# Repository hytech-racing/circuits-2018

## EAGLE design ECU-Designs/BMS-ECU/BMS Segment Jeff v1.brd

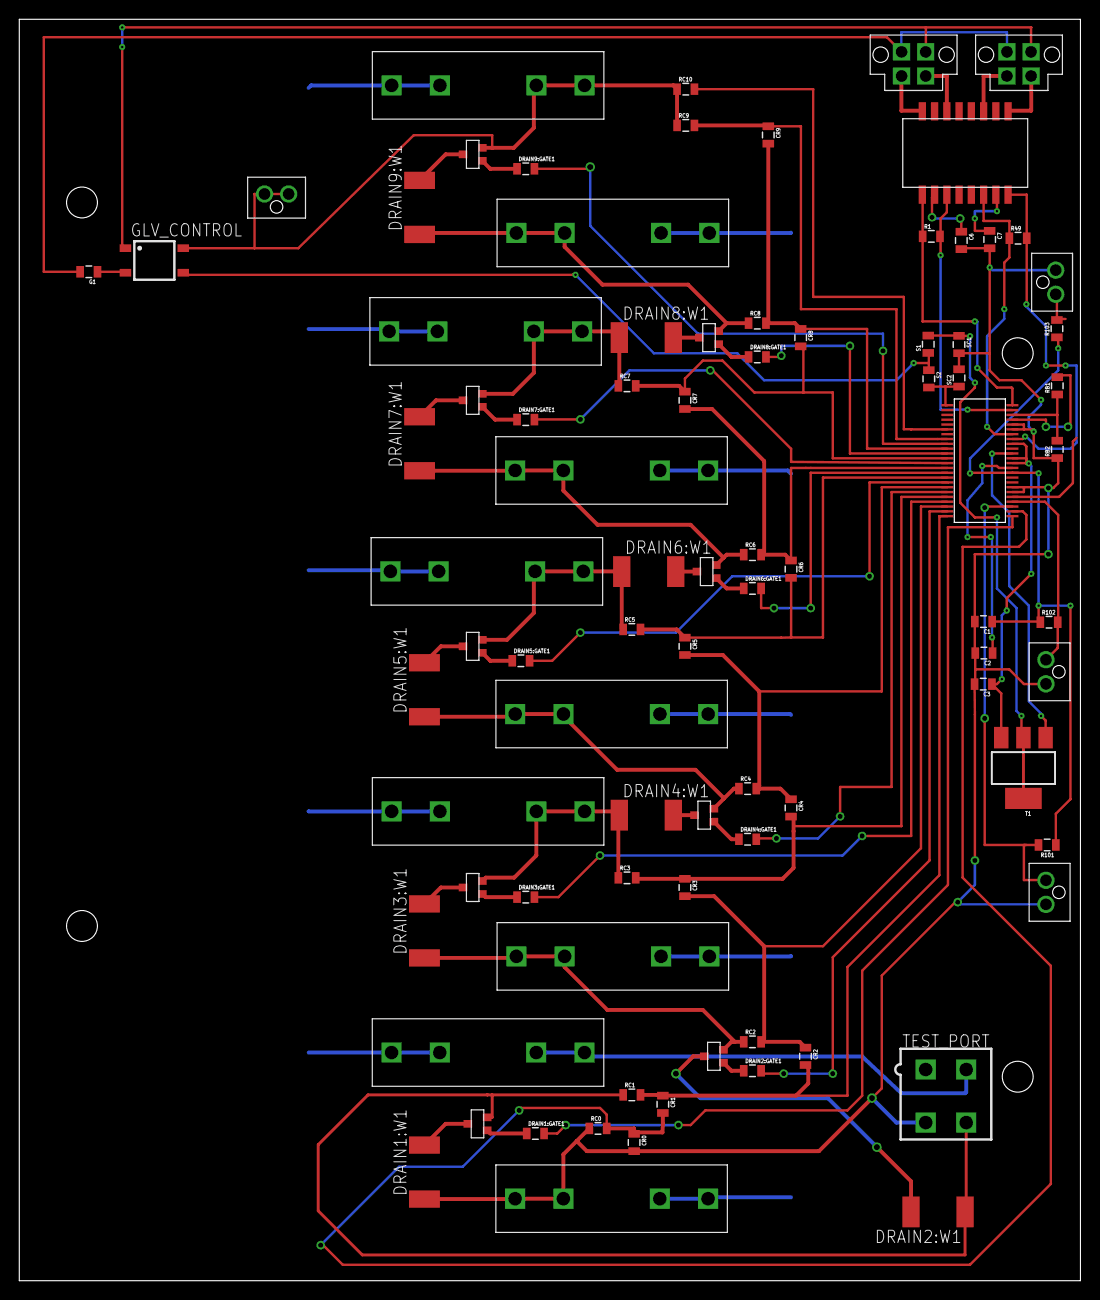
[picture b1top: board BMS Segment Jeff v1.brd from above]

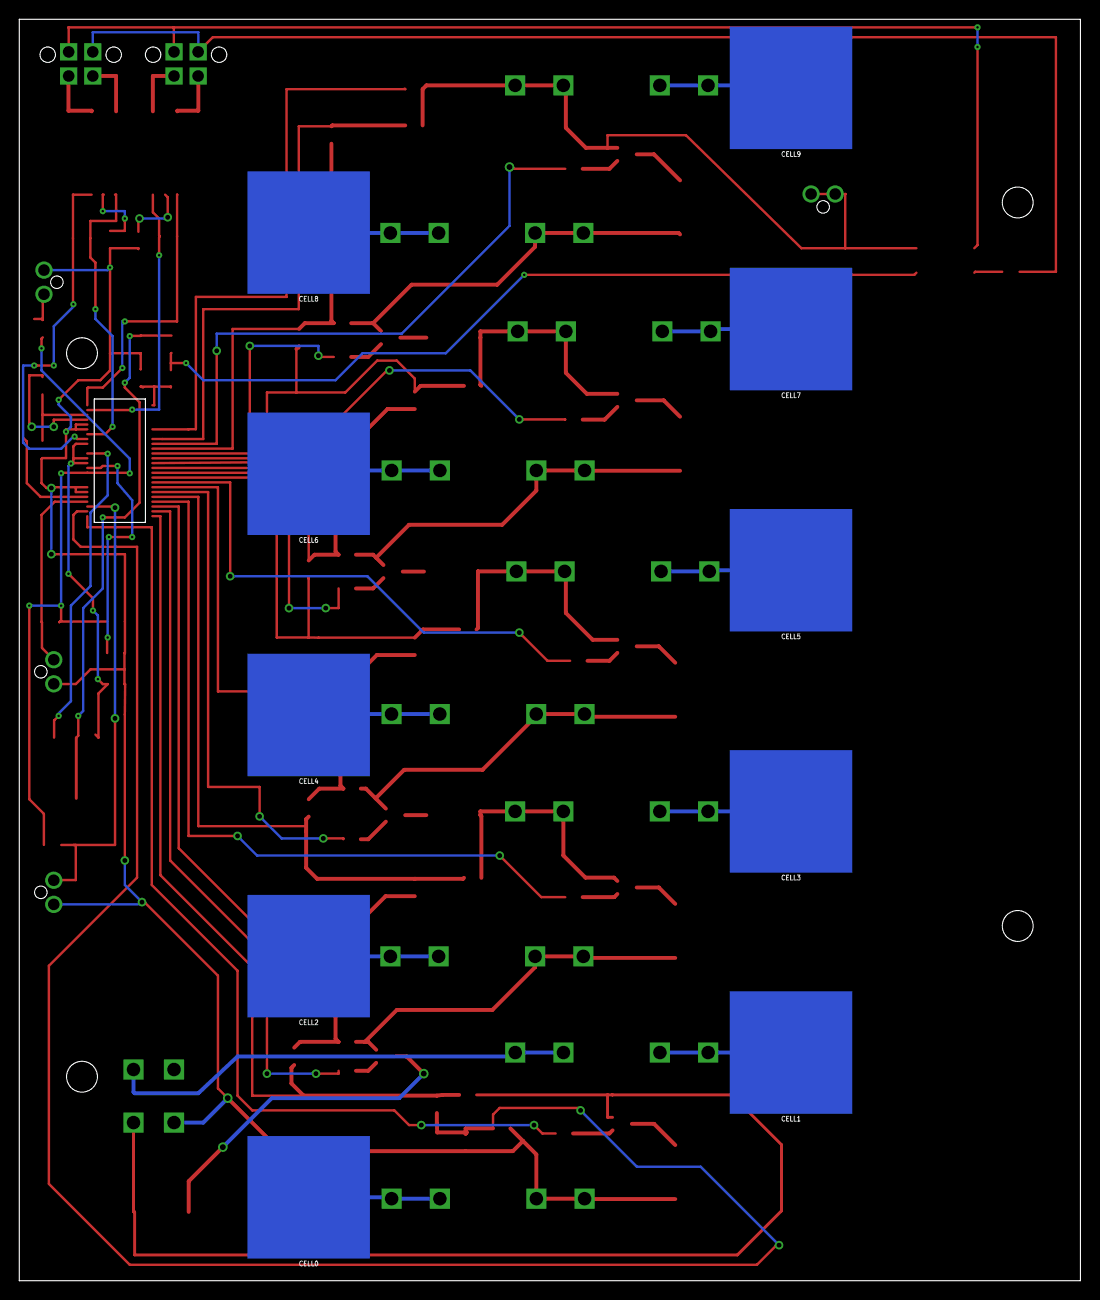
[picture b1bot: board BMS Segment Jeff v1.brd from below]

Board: 2 copper layers, 110.0 x 130.8 mm, 96 parts (10 on the bottom side), 84 nets.

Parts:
BMSIN: CONNECTOR-4NANO-FIT-VERTICAL-4; NANO-FIT_VERTICAL-4
BMSOUT: CONNECTOR-4NANO-FIT-VERTICAL-4; NANO-FIT_VERTICAL-4
C1, C2, C3: 1uF; 0805
C6, C7: 25pF; 0805
CELL0, CELL1, CELL2, CELL3, CELL4, CELL5, CELL6, CELL7, CELL8, CELL9: KEYSTONE5222
CR0, CR1, CR2, CR3, CR4, CR5, CR6, CR7, CR8, CR9: 10nF; 0805
DRAIN1:GATE1, DRAIN2:GATE1, DRAIN3:GATE1, DRAIN4:GATE1, DRAIN5:GATE1, DRAIN6:GATE1, DRAIN7:GATE1, DRAIN8:GATE1, DRAIN9:GATE1: 3.3kΩ; 0805
DRAIN1:PFET1, DRAIN2:PFET1, DRAIN3:PFET1, DRAIN4:PFET1, DRAIN5:PFET1, DRAIN6:PFET1, DRAIN7:PFET1, DRAIN8:PFET1, DRAIN9:PFET1: P-CHANNEL_MOSFET_DMP3099L-7; SOT23
DRAIN1:W1, DRAIN2:W1, DRAIN3:W1, DRAIN4:W1, DRAIN5:W1, DRAIN6:W1, DRAIN7:W1, DRAIN8:W1, DRAIN9:W1: 33Ω; R2512
F0, F1, F2, F3, F4, F5, F6, F7, F8, F9: 0751.0110
G1: 100Ω; 0805
GLV_CONTROL: CPC1002N; SOP04
R1, R49: 120Ω; 0805
R101, R102, R103: 10kΩ; 0805
RB1, RB2: 1.2k; 0805
RC0, RC1, RC2, RC3, RC4, RC5, RC6, RC7, RC8, RC9, RC10: 100Ω; 0805
S1, S2: 100Ω; 0805
SC1, SC2: 0.1uF; 0805
T1: NPN_BCP56T1; SOT223
TEST_PORT: MINIFIT_5566-4
TO_TOP: CONNECTOR-2NANO-FIT_VERTICAL-2; NANO-FIT_VERTICAL-2
TRANSFORMER-: 350uH; 749010013
U$2: LTC6804
X3: Th1; NANO-FIT_VERTICAL-2
X4: Th2; NANO-FIT_VERTICAL-2
X5: Th3; NANO-FIT_VERTICAL-2

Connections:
C0: CR0.1, CR1.2, RC0.2, U$2.26
C1: CR1.1, CR2.2, RC1.2, U$2.24
C2: CR2.1, CR3.2, RC2.2, U$2.22
C3: CR3.1, CR4.2, RC3.2, U$2.20
C4: CR4.1, CR5.2, RC4.2, U$2.18
C5: CR5.1, CR6.2, RC5.2, U$2.16
C6: CR6.1, CR7.2, RC6.2, U$2.14
C7: CR7.1, CR8.2, RC7.2, U$2.12
C8: CR8.1, CR9.2, RC8.2, U$2.10
C9: CR9.1, RC9.2, U$2.8
C10: RC10.2, U$2.6
CC0: CELL0.P$1, F0.L1, F0.L2
CC1: CELL1.P$1, F1.L1, F1.L2
CC2: CELL2.P$1, F2.L1, F2.L2
CC3: CELL3.P$1, F3.L1, F3.L2
CC4: CELL4.P$1, F4.L1, F4.L2
CC5: CELL5.P$1, F5.L1, F5.L2
CC6: CELL6.P$1, F6.L1, F6.L2
CC7: CELL7.P$1, F7.L1, F7.L2
CC8: CELL8.P$1, F8.L1, F8.L2
CC9: CELL9.P$1, F9.L1, F9.L2
DRAIN1:DRAIN: DRAIN1:PFET1.3, DRAIN1:W1.2
DRAIN1:GATE: DRAIN1:GATE1.1, DRAIN1:PFET1.1
DRAIN2:DRAIN: DRAIN2:PFET1.3, DRAIN2:W1.2
DRAIN2:GATE: DRAIN2:GATE1.1, DRAIN2:PFET1.1
DRAIN3:DRAIN: DRAIN3:PFET1.3, DRAIN3:W1.2
DRAIN3:GATE: DRAIN3:GATE1.1, DRAIN3:PFET1.1
DRAIN4:DRAIN: DRAIN4:PFET1.3, DRAIN4:W1.2
DRAIN4:GATE: DRAIN4:GATE1.1, DRAIN4:PFET1.1
DRAIN5:DRAIN: DRAIN5:PFET1.3, DRAIN5:W1.2
DRAIN5:GATE: DRAIN5:GATE1.1, DRAIN5:PFET1.1
DRAIN6:DRAIN: DRAIN6:PFET1.3, DRAIN6:W1.2
DRAIN6:GATE: DRAIN6:GATE1.1, DRAIN6:PFET1.1
DRAIN7:DRAIN: DRAIN7:PFET1.3, DRAIN7:W1.2
DRAIN7:GATE: DRAIN7:GATE1.1, DRAIN7:PFET1.1
DRAIN8:DRAIN: DRAIN8:PFET1.3, DRAIN8:W1.2
DRAIN8:GATE: DRAIN8:GATE1.1, DRAIN8:PFET1.1
DRAIN9:DRAIN: DRAIN9:PFET1.3, DRAIN9:W1.2
DRAIN9:GATE: DRAIN9:GATE1.1, DRAIN9:PFET1.1
DRIVE: T1.1, U$2.38
GND: BMSIN.P$2, BMSOUT.P$2, G1.2
ISOSPI-M_IN: BMSIN.P$3, TRANSFORMER-.8
ISOSPI-M_OUT: BMSOUT.P$3, TRANSFORMER-.3
ISOSPI-P_IN: BMSIN.P$4, TRANSFORMER-.6
ISOSPI-P_OUT: BMSOUT.P$4, TRANSFORMER-.1
unnamed: C7.1, TRANSFORMER-.10
unnamed: C6.1, TRANSFORMER-.15
unnamed: RB1.2, U$2.45
unnamed: R1.1, TRANSFORMER-.16, U$2.48
unnamed: RB1.1, RB2.2, U$2.46
unnamed: R49.1, TRANSFORMER-.11, U$2.42
unnamed: R49.2, TRANSFORMER-.9, U$2.41
unnamed: R1.2, TRANSFORMER-.14, U$2.47
S1: DRAIN1:GATE1.2, U$2.25
S2: DRAIN2:GATE1.2, U$2.23
S3: DRAIN3:GATE1.2, U$2.21
S4: DRAIN4:GATE1.2, U$2.19
S5: DRAIN5:GATE1.2, U$2.17
S6: DRAIN6:GATE1.2, U$2.15
S7: DRAIN7:GATE1.2, U$2.13
S8: DRAIN8:GATE1.2, U$2.11
S9: DRAIN9:GATE1.2, U$2.9
SENSE1: F1.R1, F1.R2, TEST_PORT.2
SENSE1_J: DRAIN1:PFET1.2, DRAIN2:W1.1, RC1.1, TEST_PORT.4
SENSE2: DRAIN2:PFET1.2, DRAIN3:W1.1, F2.R1, F2.R2, RC2.1
SENSE3: DRAIN3:PFET1.2, DRAIN4:W1.1, F3.R1, F3.R2, RC3.1
SENSE4: DRAIN4:PFET1.2, DRAIN5:W1.1, F4.R1, F4.R2, RC4.1
SENSE5: DRAIN5:PFET1.2, DRAIN6:W1.1, F5.R1, F5.R2, RC5.1
SENSE6: DRAIN6:PFET1.2, DRAIN7:W1.1, F6.R1, F6.R2, RC6.1
SENSE7: DRAIN7:PFET1.2, DRAIN8:W1.1, F7.R1, F7.R2, RC7.1
SENSE8: DRAIN8:PFET1.2, DRAIN9:W1.1, F8.R1, F8.R2, RC8.1
SENSE9: DRAIN9:PFET1.2, F9.R1, F9.R2, GLV_CONTROL.4, RC9.1, RC10.1, TO_TOP.P$1, TO_TOP.P$2
SHUTDOWN_CIRCUIT: BMSIN.P$1, BMSOUT.P$1, GLV_CONTROL.1
SSR-: G1.1, GLV_CONTROL.2
SUPPLY: S1.2, SC1.1, T1.2, T1.4
SUPPLY_INTER: GLV_CONTROL.3, S1.1, S2.1
THERMISTOR1: R101.2, U$2.27, X5.P$2
THERMISTOR2: R102.2, U$2.28, X4.P$2
THERMISTOR3: R103.2, U$2.29, X3.P$2
V+: S2.2, SC2.1, U$2.1
V-: C1.2, C2.2, C3.2, C6.2, C7.2, CR0.2, DRAIN1:W1.1, F0.R1, F0.R2, RB2.1, RC0.1, SC1.2, SC2.2, TEST_PORT.3, U$2.30, U$2.31, U$2.43, U$2.44, X3.P$1, X4.P$1, X5.P$1
VREF1: C2.1, U$2.35
VREF2: C1.1, R101.1, R102.1, R103.1, U$2.34
VREG: C3.1, T1.3, U$2.36, U$2.37, U$2.40

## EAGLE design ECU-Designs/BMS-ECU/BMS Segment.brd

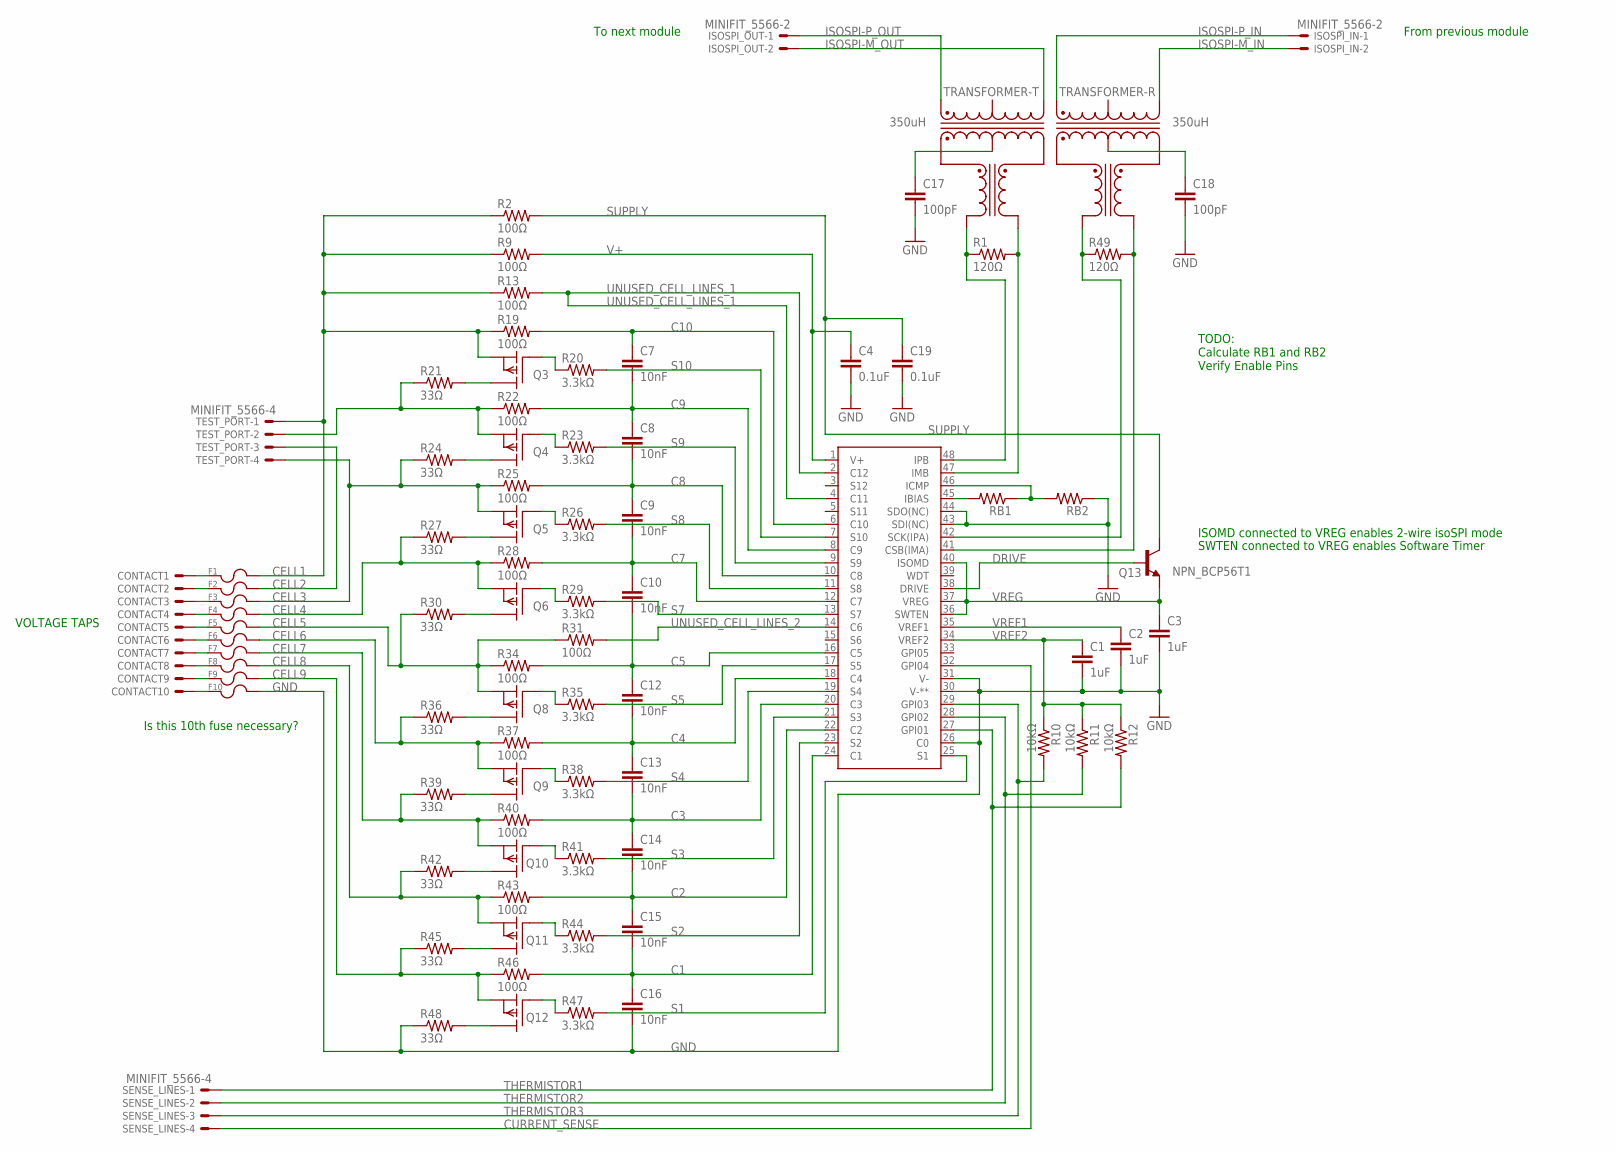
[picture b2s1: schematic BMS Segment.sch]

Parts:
C1, C2, C3: 1uF; 0805
C4, C19: 0.1uF; 0805
C7, C8, C9, C10, C12, C13, C14, C15, C16: 10nF; 0805
C17, C18: 100pF; 0805
CONTACT1, CONTACT2, CONTACT3, CONTACT4, CONTACT5, CONTACT6, CONTACT7, CONTACT8, CONTACT9, CONTACT10: SPRING_CONTACT; S1791-42R
F1, F2, F3, F4, F5, F6, F7, F8, F9, F10: 0751.0110_FUSE_CLIP; 0751.0110
ISOSPI_IN: MINIFIT_5566-2
ISOSPI_OUT: MINIFIT_5566-2
Q3, Q4, Q5, Q6, Q8, Q9, Q10, Q11, Q12: P-CHANNEL_MOSFET_DMP3099L-7; SOT23
Q13: NPN_BCP56T1; SOT223
R1, R49: 120Ω; 0805
R2, R9, R13, R19, R22, R25, R28, R31, R34, R37, R40, R43, R46: 100Ω; 0805
R10, R11, R12: 10kΩ; 0805
R20, R23, R26, R29, R35, R38, R41, R44, R47: 3.3kΩ; 0805
R21, R24, R27, R30, R36, R39, R42, R45, R48: 33Ω; R2512
RB1, RB2: RESISTOR0805-RES; 0805
SENSE_LINES: MINIFIT_5566-4
TEST_PORT: MINIFIT_5566-4
TRANSFORMER-: 350uH; 749010013
U$2: LTC6804-1; LTC6804

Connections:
C1: C15.2, C16.1, R46.2, U$2.24 (C1)
C2: C14.2, C15.1, R43.2, U$2.22 (C2)
C3: C13.2, C14.1, R40.2, U$2.20 (C3)
C4: C12.2, C13.1, R37.2, U$2.18 (C4)
C5: C10.2, C12.1, R34.2, U$2.16 (C5)
C7: C9.2, C10.1, R28.2, U$2.12 (C7)
C8: C8.2, C9.1, R25.2, U$2.10 (C8)
C9: C7.2, C8.1, R22.2, U$2.8 (C9)
C10: C7.1, R19.2, U$2.6 (C10)
CELL1: F1.R1 (2), F1.R2 (2), Q3.2 (S), R2.1, R9.1, R13.1, R19.1, TEST_PORT.1
CELL2: F2.R1 (2), F2.R2 (2), Q4.2 (S), R21.1, R22.1, TEST_PORT.2, TEST_PORT.3
CELL3: F3.R1 (2), F3.R2 (2), Q5.2 (S), R24.1, R25.1, TEST_PORT.4
CELL4: F4.R1 (2), F4.R2 (2), Q6.2 (S), R27.1, R28.1
CELL5: F5.R1 (2), F5.R2 (2), Q8.2 (S), R30.1, R31.1, R34.1
CELL6: F6.R1 (2), F6.R2 (2), Q9.2 (S), R36.1, R37.1
CELL7: F7.R1 (2), F7.R2 (2), Q10.2 (S), R39.1, R40.1
CELL8: F8.R1 (2), F8.R2 (2), Q11.2 (S), R42.1, R43.1
CELL9: F9.R1 (2), F9.R2 (2), Q12.2 (S), R45.1, R46.1
CURRENT_SENSE: SENSE_LINES.4, U$2.32 (GPI04)
DRIVE: Q13.1 (BASE), U$2.38 (DRIVE)
GND: C1.2, C2.2, C3.2, C4.2, C16.2, C17.2, C18.2, C19.2, F10.R1 (2), F10.R2 (2), R48.1, RB2.1, U$2.26 (C0), U$2.30 (V-**), U$2.31 (V-), U$2.43 (SDI(NC)), U$2.44 (SDO(NC))
ISOSPI-M_IN: ISOSPI_IN.2, TRANSFORMER-.8 (D-)
ISOSPI-M_OUT: ISOSPI_OUT.2, TRANSFORMER-.3 (D-)
ISOSPI-P_IN: ISOSPI_IN.1, TRANSFORMER-.6 (D+)
ISOSPI-P_OUT: ISOSPI_OUT.1, TRANSFORMER-.1 (D+)
unnamed: C18.1, TRANSFORMER-.10 (CX)
unnamed: C17.1, TRANSFORMER-.15 (CX)
unnamed: RB1.2, U$2.45 (IBIAS)
unnamed: R1.1, TRANSFORMER-.16 (X+), U$2.48 (IPB)
unnamed: RB1.1, RB2.2, U$2.46 (ICMP)
unnamed: R49.1, TRANSFORMER-.11 (X+), U$2.42 (SCK(IPA))
unnamed: R49.2, TRANSFORMER-.9 (X-), U$2.41 (CSB(IMA))
unnamed: CONTACT1.P$1, F1.L1 (1), F1.L2 (1)
unnamed: Q3.1 (G), R20.1
unnamed: CONTACT2.P$1, F2.L1 (1), F2.L2 (1)
unnamed: CONTACT3.P$1, F3.L1 (1), F3.L2 (1)
unnamed: Q3.3 (D), R21.2
unnamed: CONTACT4.P$1, F4.L1 (1), F4.L2 (1)
unnamed: Q8.1 (G), R35.1
unnamed: Q9.1 (G), R38.1
unnamed: CONTACT5.P$1, F5.L1 (1), F5.L2 (1)
unnamed: CONTACT6.P$1, F6.L1 (1), F6.L2 (1)
unnamed: Q4.3 (D), R24.2
unnamed: CONTACT7.P$1, F7.L1 (1), F7.L2 (1)
unnamed: Q10.1 (G), R41.1
unnamed: Q11.1 (G), R44.1
unnamed: Q12.1 (G), R47.1
unnamed: Q5.3 (D), R27.2
unnamed: CONTACT8.P$1, F8.L1 (1), F8.L2 (1)
unnamed: CONTACT9.P$1, F9.L1 (1), F9.L2 (1)
unnamed: CONTACT10.P$1, F10.L1 (1), F10.L2 (1)
unnamed: Q6.3 (D), R30.2
unnamed: R1.2, TRANSFORMER-.14 (X-), U$2.47 (IMB)
unnamed: Q8.3 (D), R36.2
unnamed: Q9.3 (D), R39.2
unnamed: Q10.3 (D), R42.2
unnamed: Q11.3 (D), R45.2
unnamed: Q12.3 (D), R48.2
unnamed: Q4.1 (G), R23.1
unnamed: Q5.1 (G), R26.1
unnamed: Q6.1 (G), R29.1
S1: R47.2, U$2.25 (S1)
S2: R44.2, U$2.23 (S2)
S3: R41.2, U$2.21 (S3)
S4: R38.2, U$2.19 (S4)
S5: R35.2, U$2.17 (S5)
S7: R29.2, U$2.13 (S7)
S8: R26.2, U$2.11 (S8)
S9: R23.2, U$2.9 (S9)
S10: R20.2, U$2.7 (S10)
SUPPLY: C19.1, Q13.2 (COLLECTOR), Q13.4 (COLLECTOR), R2.2
THERMISTOR1: R12.2, SENSE_LINES.1, U$2.27 (GPI01)
THERMISTOR2: R11.2, SENSE_LINES.2, U$2.28 (GPI02)
THERMISTOR3: R10.2, SENSE_LINES.3, U$2.29 (GPI03)
UNUSED_CELL_LINES_1: R13.2, U$2.2 (C12), U$2.4 (C11)
UNUSED_CELL_LINES_2: R31.2, U$2.14 (C6)
V+: C4.1, R9.2, U$2.1 (V+)
VREF1: C2.1, U$2.35 (VREF1)
VREF2: C1.1, R10.1, R11.1, R12.1, U$2.34 (VREF2)
VREG: C3.1, Q13.3 (EMITTER), U$2.36 (SWTEN), U$2.37 (VREG), U$2.40 (ISOMD)

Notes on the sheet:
SWTEN connected to VREG enables Software Timer
ISOMD connected to VREG enables 2-wire isoSPI mode
VOLTAGE TAPS
To next module
From previous module
TODO: Calculate RB1 and RB2 Verify Enable Pins
Is this 10th fuse necessary?

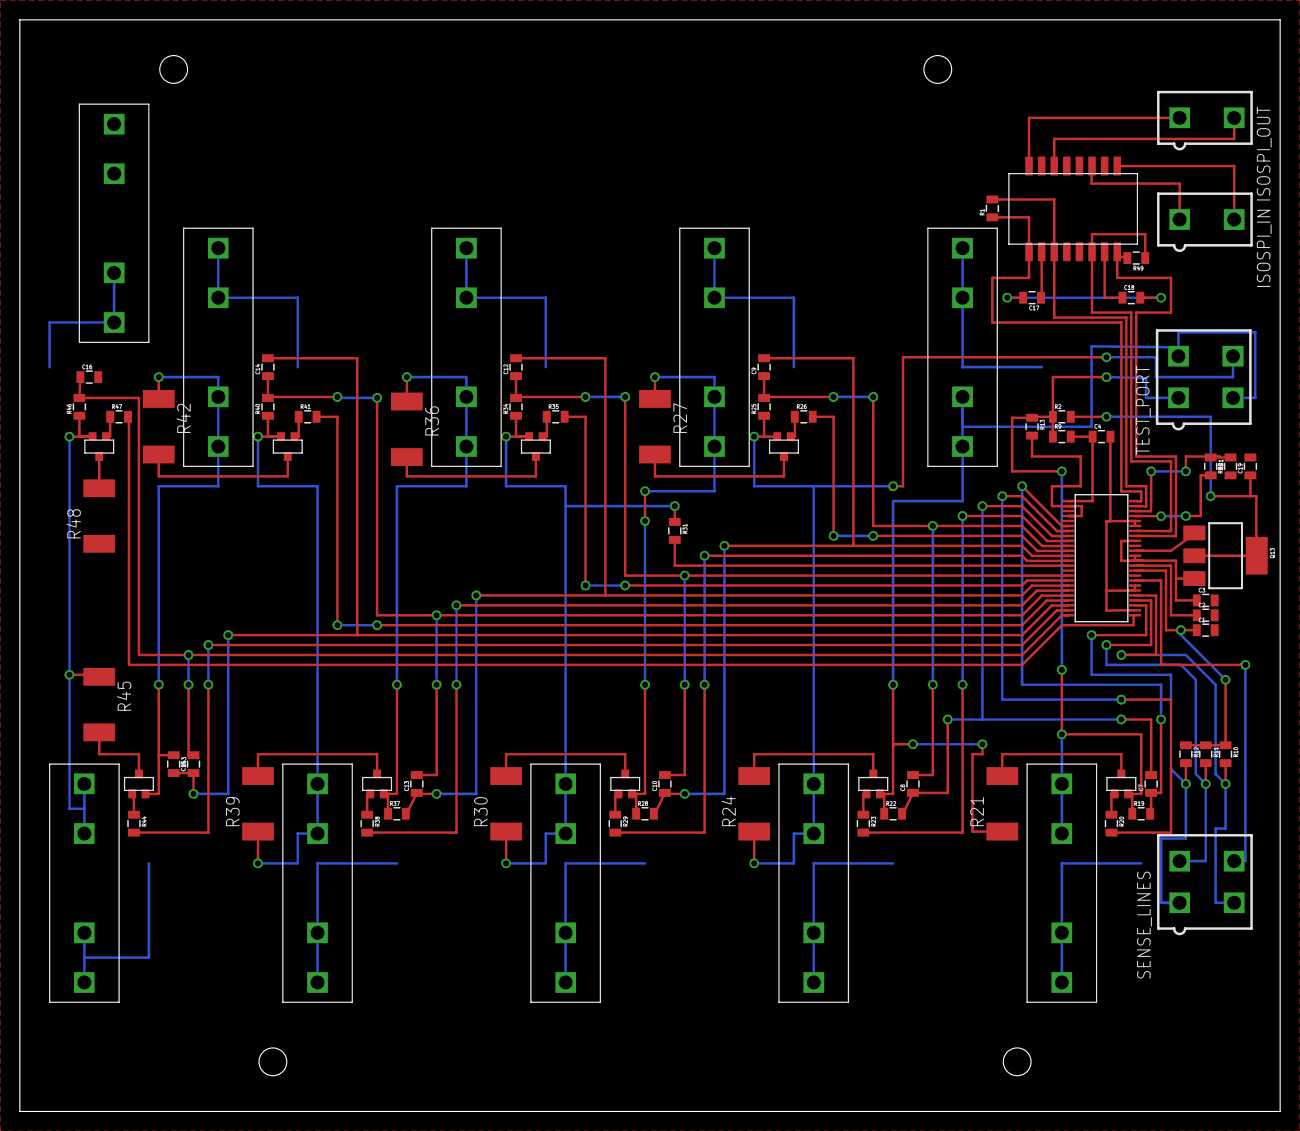
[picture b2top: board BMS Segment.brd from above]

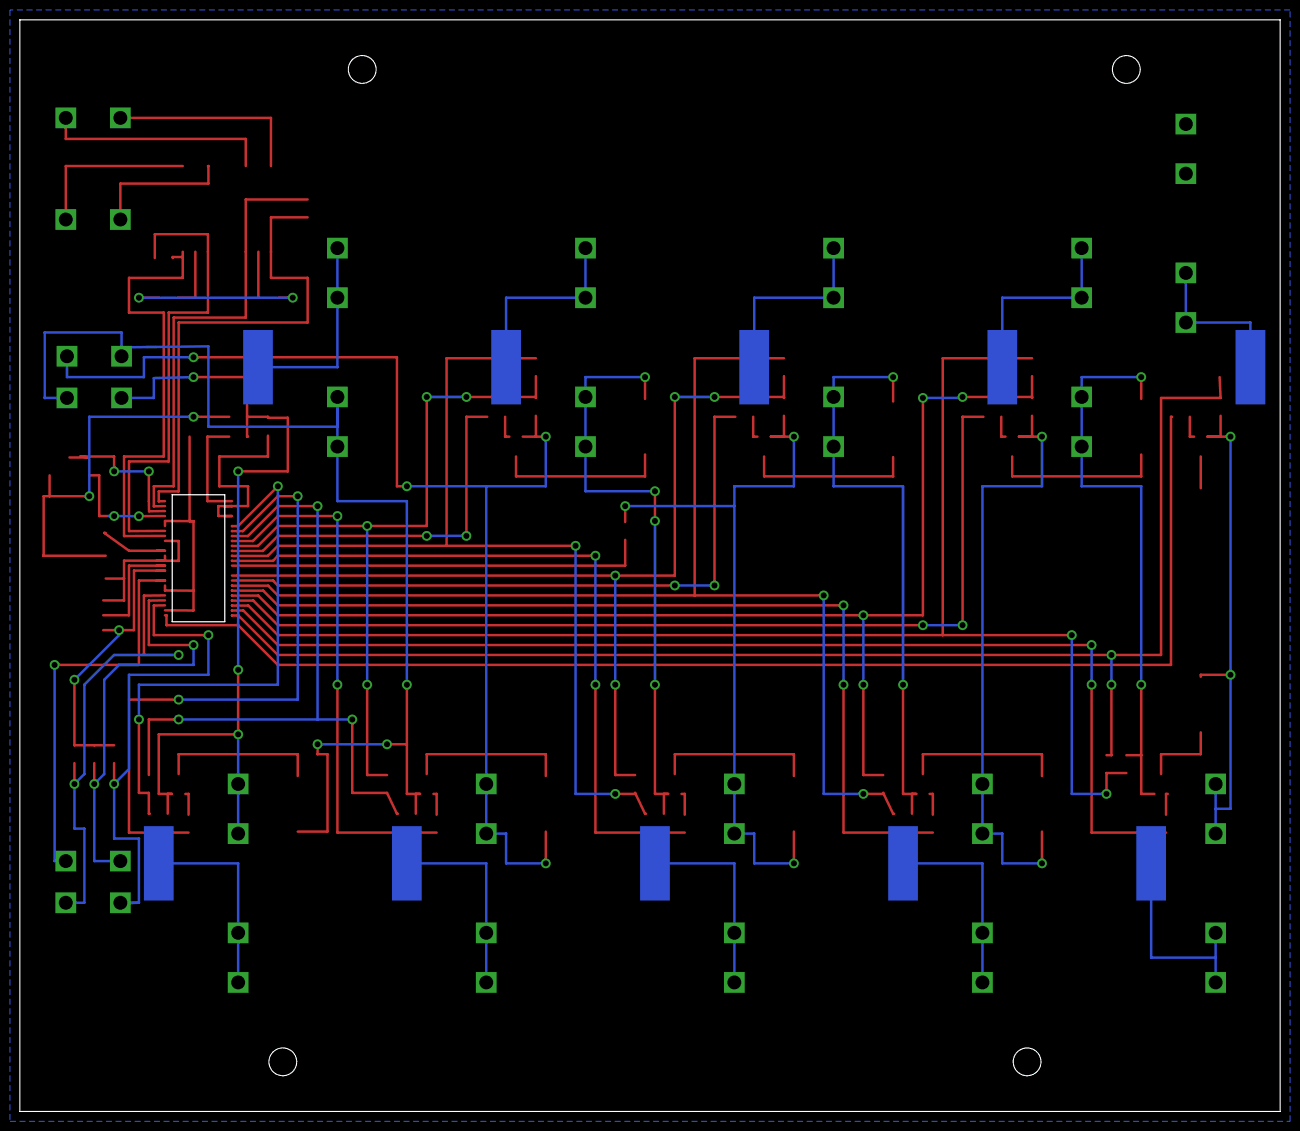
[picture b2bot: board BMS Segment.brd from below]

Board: 2 copper layers, 127.0 x 110.0 mm, 90 parts (10 on the bottom side), 80 nets.

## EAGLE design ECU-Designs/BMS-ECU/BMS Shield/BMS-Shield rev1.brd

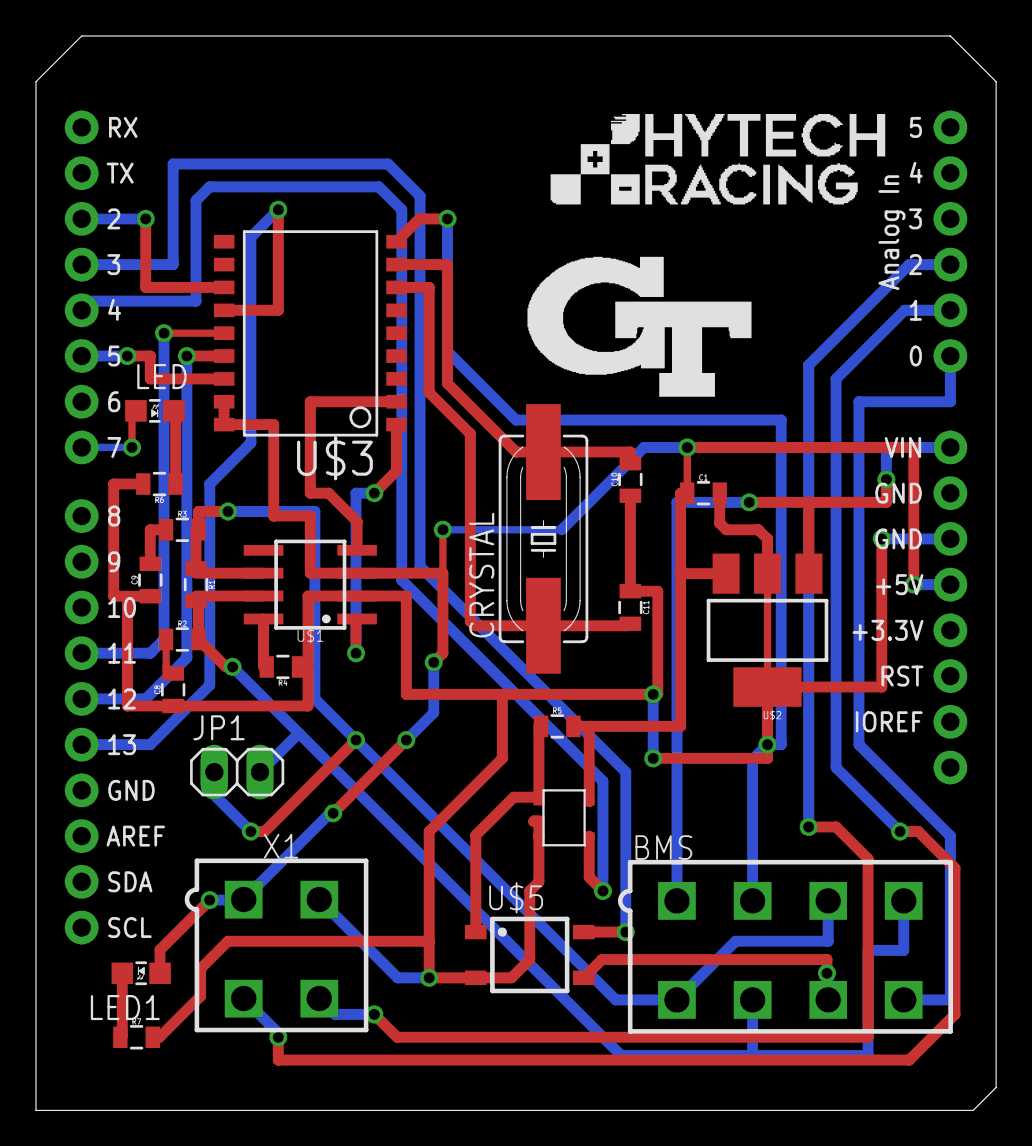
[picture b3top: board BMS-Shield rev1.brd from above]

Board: 2 copper layers, 53.3 x 59.7 mm, 24 parts (0 on the bottom side), 27 nets.

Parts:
BMS: MINIFIT_5566-8
C1: 0.1uF; 0805
C8, C9: 560pF; 0805
C10, C11: 22pF; 0805
CRYSTAL: 16MHz; HC49UP
J1: ARDUINO_R3_SHIELD; UNO_R3_SHIELD
JP1: M02; 1X02
LED, LED1: LED-805
R1: 120; 0805
R2, R3: 100; 0805
R4: 1k; 0805
R5: 68; 0805
R6, R7: 0805
U$1: MCP2551; SOIC-08
U$2: SOT223
U$3: MCP2515SMD; SOIC-18W
U$4: STWD100; SOT23-5
U$5: CPC1002N; SOP04
X1: CONNECTOR-4; MINIFIT_5566-4

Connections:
12V_SUPPLY: BMS.1, J1.VIN, U$2.1
+5V: C1.1, J1.5V, LED1.A, R5.2, U$1.3, U$2.3, U$3.17, U$3.18, U$4.VCC, X1.1
CANH: BMS.4, BMS.6, JP1.2, R1.2, R2.2, U$1.7
CANL: BMS.3, BMS.5, JP1.1, R1.1, R3.2, U$1.6
CS: J1.D5, U$3.16
GND: BMS.2, C1.2, C8.1, C9.1, C10.1, C11.1, J1.GND@0, R4.1, R6.2, R7.2, U$1.2, U$2.2, U$2.4, U$3.9, U$4.EN, U$4.GND, U$5.2, X1.2
unnamed: BMS.8, J1.A0
unnamed: J1.D12, U$3.15
unnamed: J1.D11, U$3.14
unnamed: J1.D13, U$3.13
unnamed: R5.1, U$4.WDO, U$5.1
unnamed: J1.D4, U$4.WDI
unnamed: J1.D7, LED.A
unnamed: BMS.7, U$5.3
unnamed: J1.D3, U$5.4
unnamed: J1.D2, U$3.12
unnamed: C10.2, CRYSTAL.2, U$3.8
unnamed: U$1.1, U$3.1
unnamed: U$1.4, U$3.2
unnamed: C8.2, R2.1
unnamed: C11.2, CRYSTAL.1, U$3.7
unnamed: R4.2, U$1.8
unnamed: C9.2, R3.1
unnamed: LED.C, R6.1
unnamed: J1.A1, X1.3
unnamed: J1.A2, X1.4
unnamed: LED1.C, R7.1

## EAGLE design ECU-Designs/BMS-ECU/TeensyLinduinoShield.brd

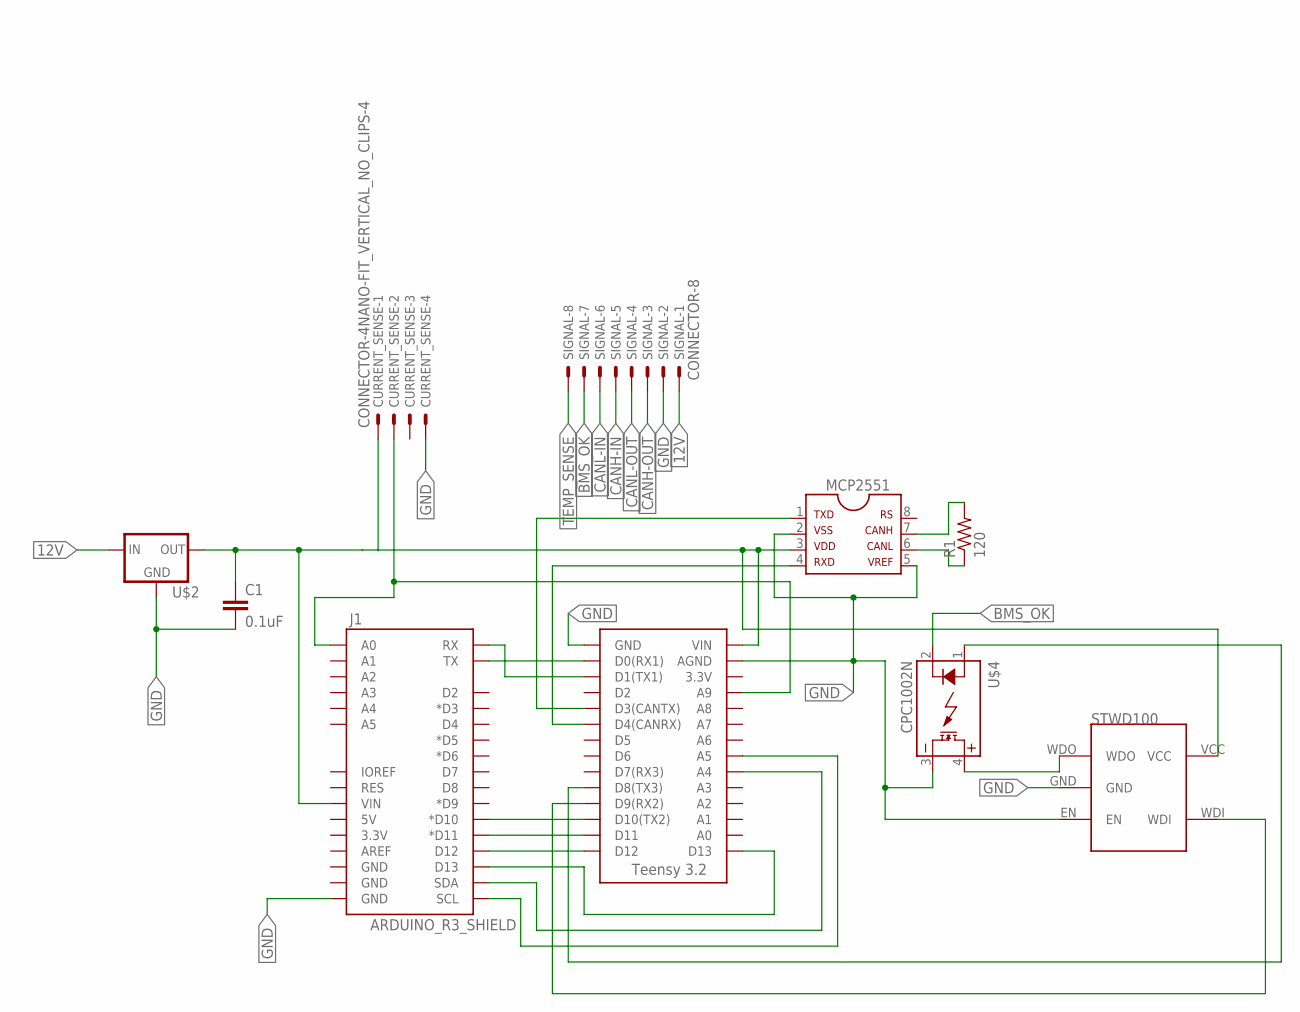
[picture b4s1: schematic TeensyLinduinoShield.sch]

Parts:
C1: 0.1uF; 0805
CURRENT_SENSE: CONNECTOR-4NANO-FIT_VERTICAL_NO_CLIPS-4; NANO-FIT_VERTICAL_NO_CLIPS-4
J1: ARDUINO_R3_SHIELD; UNO_R3_SHIELD
MCP2551: MCP2551; SOIC-08
R1: 120; 0805
SIGNAL: CONNECTOR-8; MINIFIT_5566-8
U$1: TEENSY_3.2_SIMPLE
U$2: 5VREG_LM340-NLM340MPX-5.0/NOPB; SOT223
U$3: STWD100; SOT23-5
U$4: CPC1002N; SOP04

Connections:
12V: SIGNAL.1, U$2.1 (IN)
BMS_OK: SIGNAL.7, U$4.2 (CONTROL-)
CANH-IN: SIGNAL.5
CANH-OUT: SIGNAL.3
CANL: MCP2551.6, R1.1
CANL-IN: SIGNAL.6
CANL-OUT: SIGNAL.4
GND: C1.2, CURRENT_SENSE.P$4, J1.GND@0 (GND), MCP2551.2, MCP2551.5, SIGNAL.2, U$1.AGND, U$1.GND, U$2.2 (GND), U$2.4 (GND), U$3.EN, U$3.GND, U$4.3 (DC-)
unnamed: J1.TX, U$1.D0(RX1)
unnamed: J1.RX, U$1.D1(TX1)
unnamed: J1.D10 (*D10), U$1.D10(TX2)
unnamed: J1.D11 (*D11), U$1.D11
unnamed: C1.1, CURRENT_SENSE.P$1, J1.VIN, MCP2551.3, U$1.VIN, U$2.3 (OUT), U$3.VCC
unnamed: J1.D12, U$1.D12
unnamed: J1.D13, U$1.D13
unnamed: MCP2551.1, U$1.D3(CANTX)
unnamed: MCP2551.4, U$1.D4(CANRX)
unnamed: J1.SCL, U$1.A5
unnamed: J1.SDA, U$1.A4
unnamed: U$1.D9(RX2), U$3.WDI
unnamed: U$3.WDO, U$4.4 (DC+)
unnamed: MCP2551.7, R1.2
unnamed: CURRENT_SENSE.P$2, J1.A0, U$1.A9
unnamed: U$1.D8(TX3), U$4.1 (CONTROL+)
TEMP_SENSE: SIGNAL.8

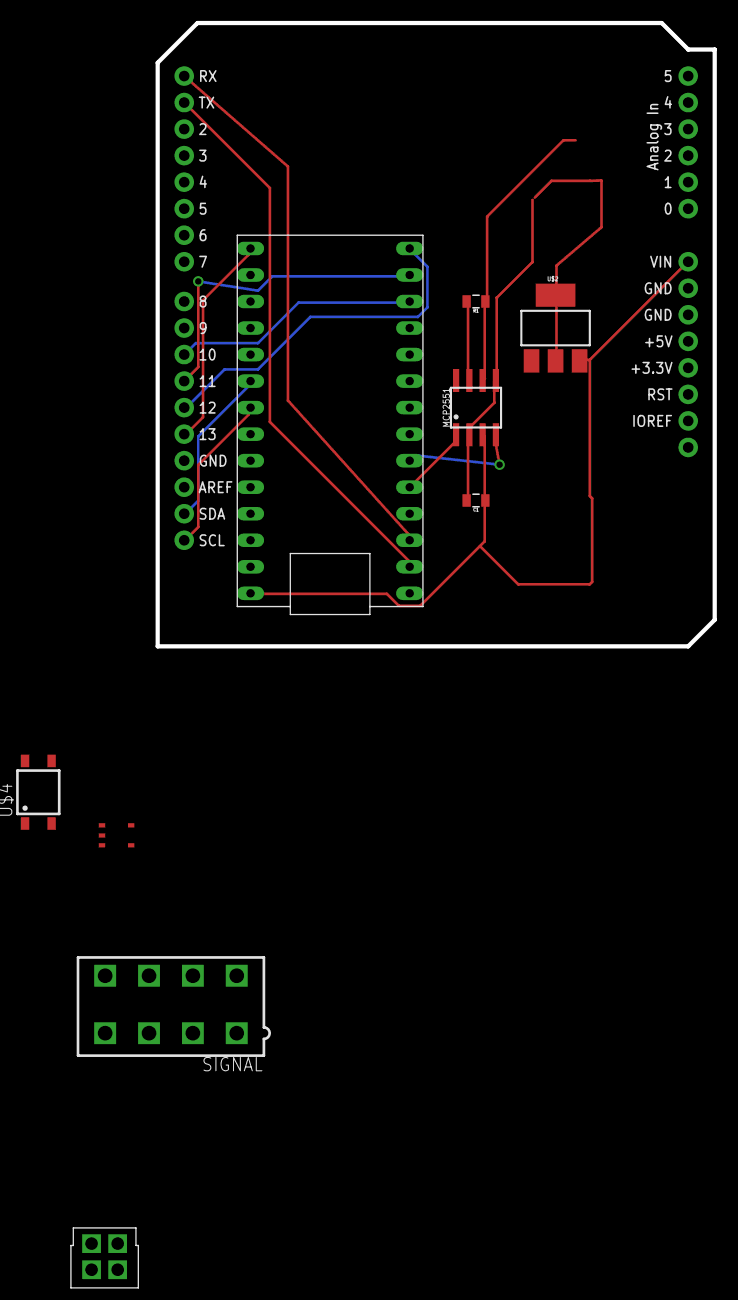
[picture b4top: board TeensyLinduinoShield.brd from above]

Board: 2 copper layers, 53.3 x 59.7 mm, 10 parts (0 on the bottom side), 20 nets.

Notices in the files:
parts and their libraries:
SparkFun-FreqCtrl: Licensing: Creative Commons ShareAlike 4.0 International - https://creativecommons.org/licenses/by-sa/4.0
